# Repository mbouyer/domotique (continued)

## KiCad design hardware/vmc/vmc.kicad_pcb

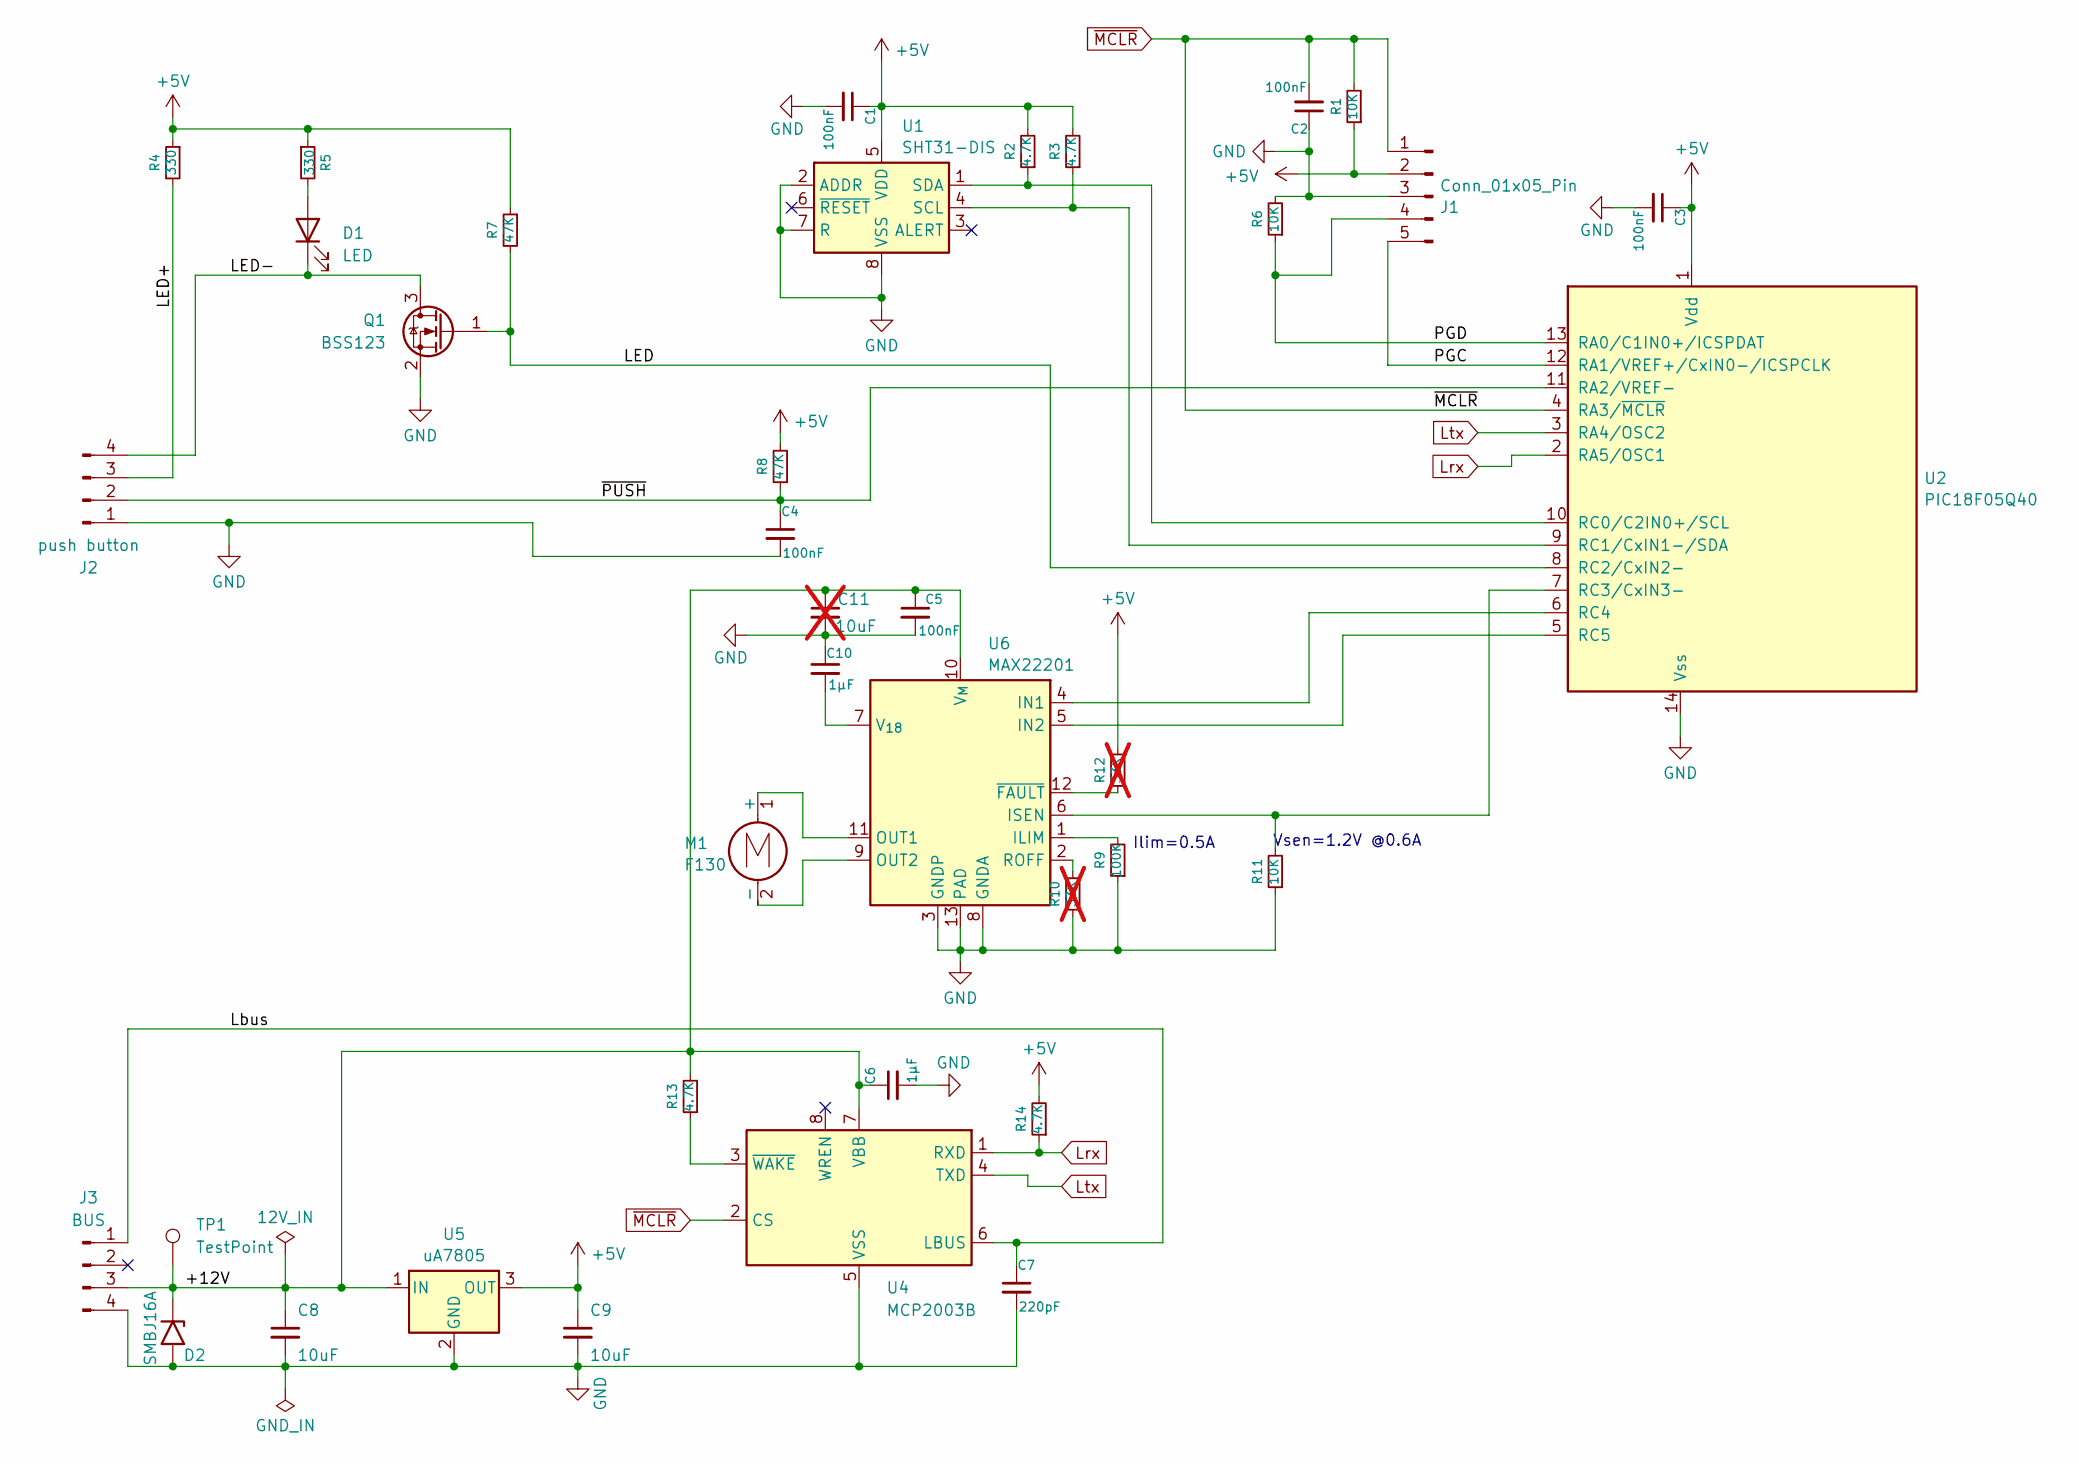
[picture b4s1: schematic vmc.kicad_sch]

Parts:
C1, C2, C3, C4, C5: 100nF; C_0603_1608Metric_Pad1.08x0.95mm_HandSolder
C6: 1µF; C_0805_2012Metric_Pad1.18x1.45mm_HandSolder
C7: 220pF; C_0603_1608Metric_Pad1.08x0.95mm_HandSolder
C8: 10uF; C_1210_3225Metric_Pad1.33x2.70mm_HandSolder
C9: 10uF; C_0805_2012Metric_Pad1.18x1.45mm_HandSolder
C10: 1µF; C_0603_1608Metric_Pad1.08x0.95mm_HandSolder
C11: 10uF; C_1210_3225Metric_Pad1.33x2.70mm_HandSolder; not fitted
D1: LED; LED_0603_1608Metric_Pad1.05x0.95mm_HandSolder
D2: SMBJ16A; D_SMB_Handsoldering
J1: Conn_01x05_Pin; Molex_Pico-SPOX-5-Vertical
J2: push button; Molex Pico-SPOX-4_90
J3: BUS; Molex Pico-SPOX-4_90
M1: F130
Q1: BSS123; SOT-23
R1, R6, R11: 10K; R_0805_2012Metric_Pad1.20x1.40mm_HandSolder
R2, R3, R13, R14: 4.7K; R_0805_2012Metric_Pad1.20x1.40mm_HandSolder
R4, R5: 330; R_0805_2012Metric_Pad1.20x1.40mm_HandSolder
R7, R8: 47K; R_0805_2012Metric_Pad1.20x1.40mm_HandSolder
R9: 100K; R_0805_2012Metric_Pad1.20x1.40mm_HandSolder
R10, R12: 33K; R_0805_2012Metric_Pad1.20x1.40mm_HandSolder; not fitted
TP1: TestPoint; TestPoint_THTPad_D1.5mm_Drill0.7mm
U1: SHT31-DIS; Sensirion_DFN-8-1EP_2.5x2.5mm_P0.5mm_EP1.1x1.7mm
U2: PIC18F05Q40; SOIC-14_3.9x8.7mm_P1.27mm
U4: MCP2003B; SOIC-8_3.9x4.9mm_P1.27mm
U5: uA7805; TO-252-3_TabPin2
U6: MAX22201; Maxim_TDFN-12-1EP_3x3mm_P0.5mm_EP1.7x2.5mm

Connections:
+5V: C1.1, C3.1, C9.1, J1.2, R1.1, R2.2, R3.2, R4.1, R5.1, R7.1, R8.2, R12.2, R14.2, U1.5 (VDD), U2.1 (Vdd), U5.3 (OUT)
/+12V: C5.1, C6.1, C8.1, C11.1, D2.1 (A1), J3.3, R13.2, TP1.1, U4.7 (VBB), U5.1 (IN), U6.10 (V_{M})
/LED: Q1.1 (G), R7.2, U2.8 (RC2/CxIN2-)
/LED+: J2.3, R4.2
/LED-: D1.1 (K), J2.4, Q1.3 (D)
/Lbus: C7.1, J3.1, U4.6 (LBUS)
/PGC: J1.5, U2.12 (RA1/VREF+/CxIN0-/ICSPCLK)
/PGD: J1.4, R6.1, U2.13 (RA0/C1IN0+/ICSPDAT)
/~PUSH: C4.1, J2.2, R8.1, U2.11 (RA2/VREF-)
GND: C1.2, C2.1, C3.2, C4.2, C5.2, C6.2, C7.2, C8.2, C9.2, C10.1, C11.2, D2.2 (A2), J1.3, J2.1, J3.4, Q1.2 (S), R6.2, R9.1, R10.1, R11.1, U1.2 (ADDR), U1.7 (R), U1.8 (VSS), U1.9 (VSS), U2.14 (Vss), U4.5 (VSS), U5.2 (GND), U6.3 (GNDP), U6.8 (GNDA), U6.13 (PAD)
Lrx: R14.1, U2.2 (RA5/OSC1), U4.1 (RXD)
Ltx: U2.3 (RA4/OSC2), U4.4 (TXD)
unnamed: D1.2 (A), R5.2
unnamed: M1.1 (+), U6.11 (OUT1)
unnamed: M1.2 (-), U6.9 (OUT2)
unnamed: R3.1, U1.4 (SCL), U2.9 (RC1/CxIN1-/SDA)
unnamed: R2.1, U1.1 (SDA), U2.10 (RC0/C2IN0+/SCL)
unnamed: R11.2, U2.7 (RC3/CxIN3-), U6.6 (ISEN)
unnamed: U2.6 (RC4), U6.4 (IN1)
unnamed: U2.5 (RC5), U6.5 (IN2)
unnamed: R13.1, U4.3 (~WAKE)
unnamed: R9.2, U6.1 (ILIM)
unnamed: R10.2, U6.2 (ROFF)
unnamed: C10.2, U6.7 (V_{18})
unnamed: R12.1, U6.12 (~FAULT)
~MCLR: C2.2, J1.1, R1.2, U2.4 (RA3/~MCLR), U4.2 (CS)

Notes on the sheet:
Ilim=0.5A
Vsen=1.2V @0.6A

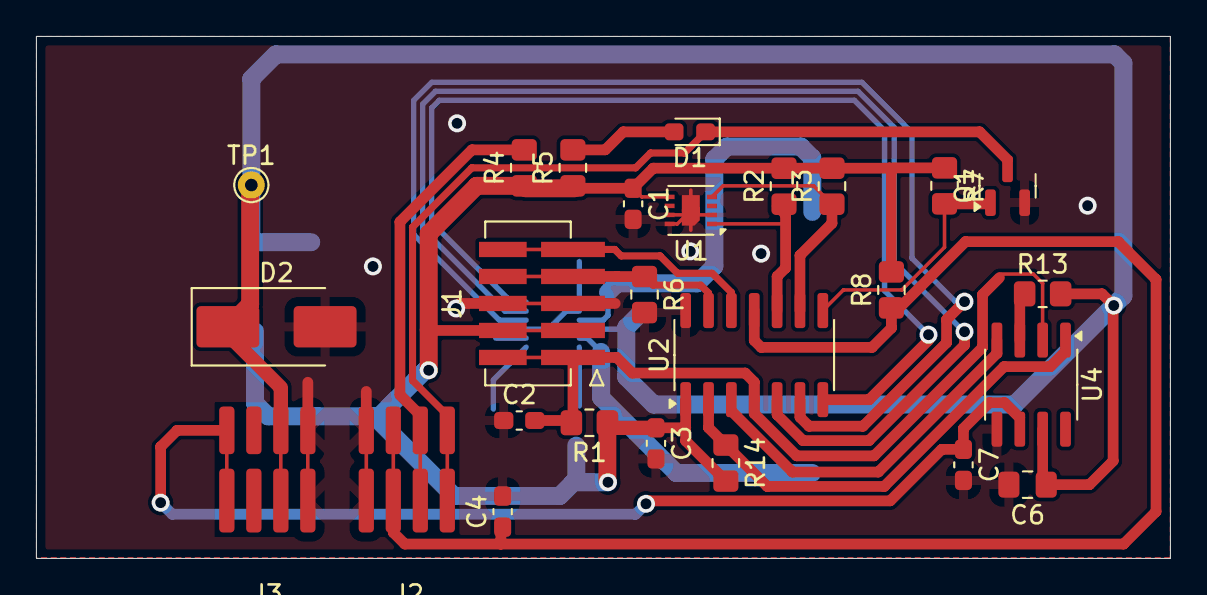
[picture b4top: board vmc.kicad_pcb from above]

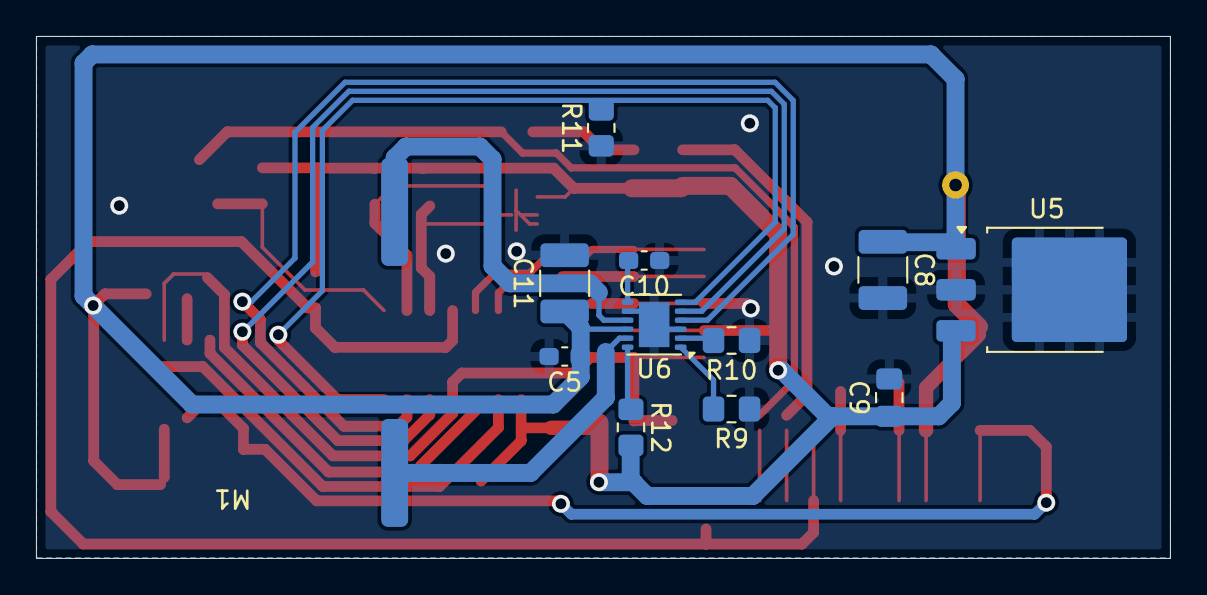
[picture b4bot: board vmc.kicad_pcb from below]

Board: 2 copper layers, 63.0 x 29.0 mm, 38 parts (12 on the bottom side), 26 nets.

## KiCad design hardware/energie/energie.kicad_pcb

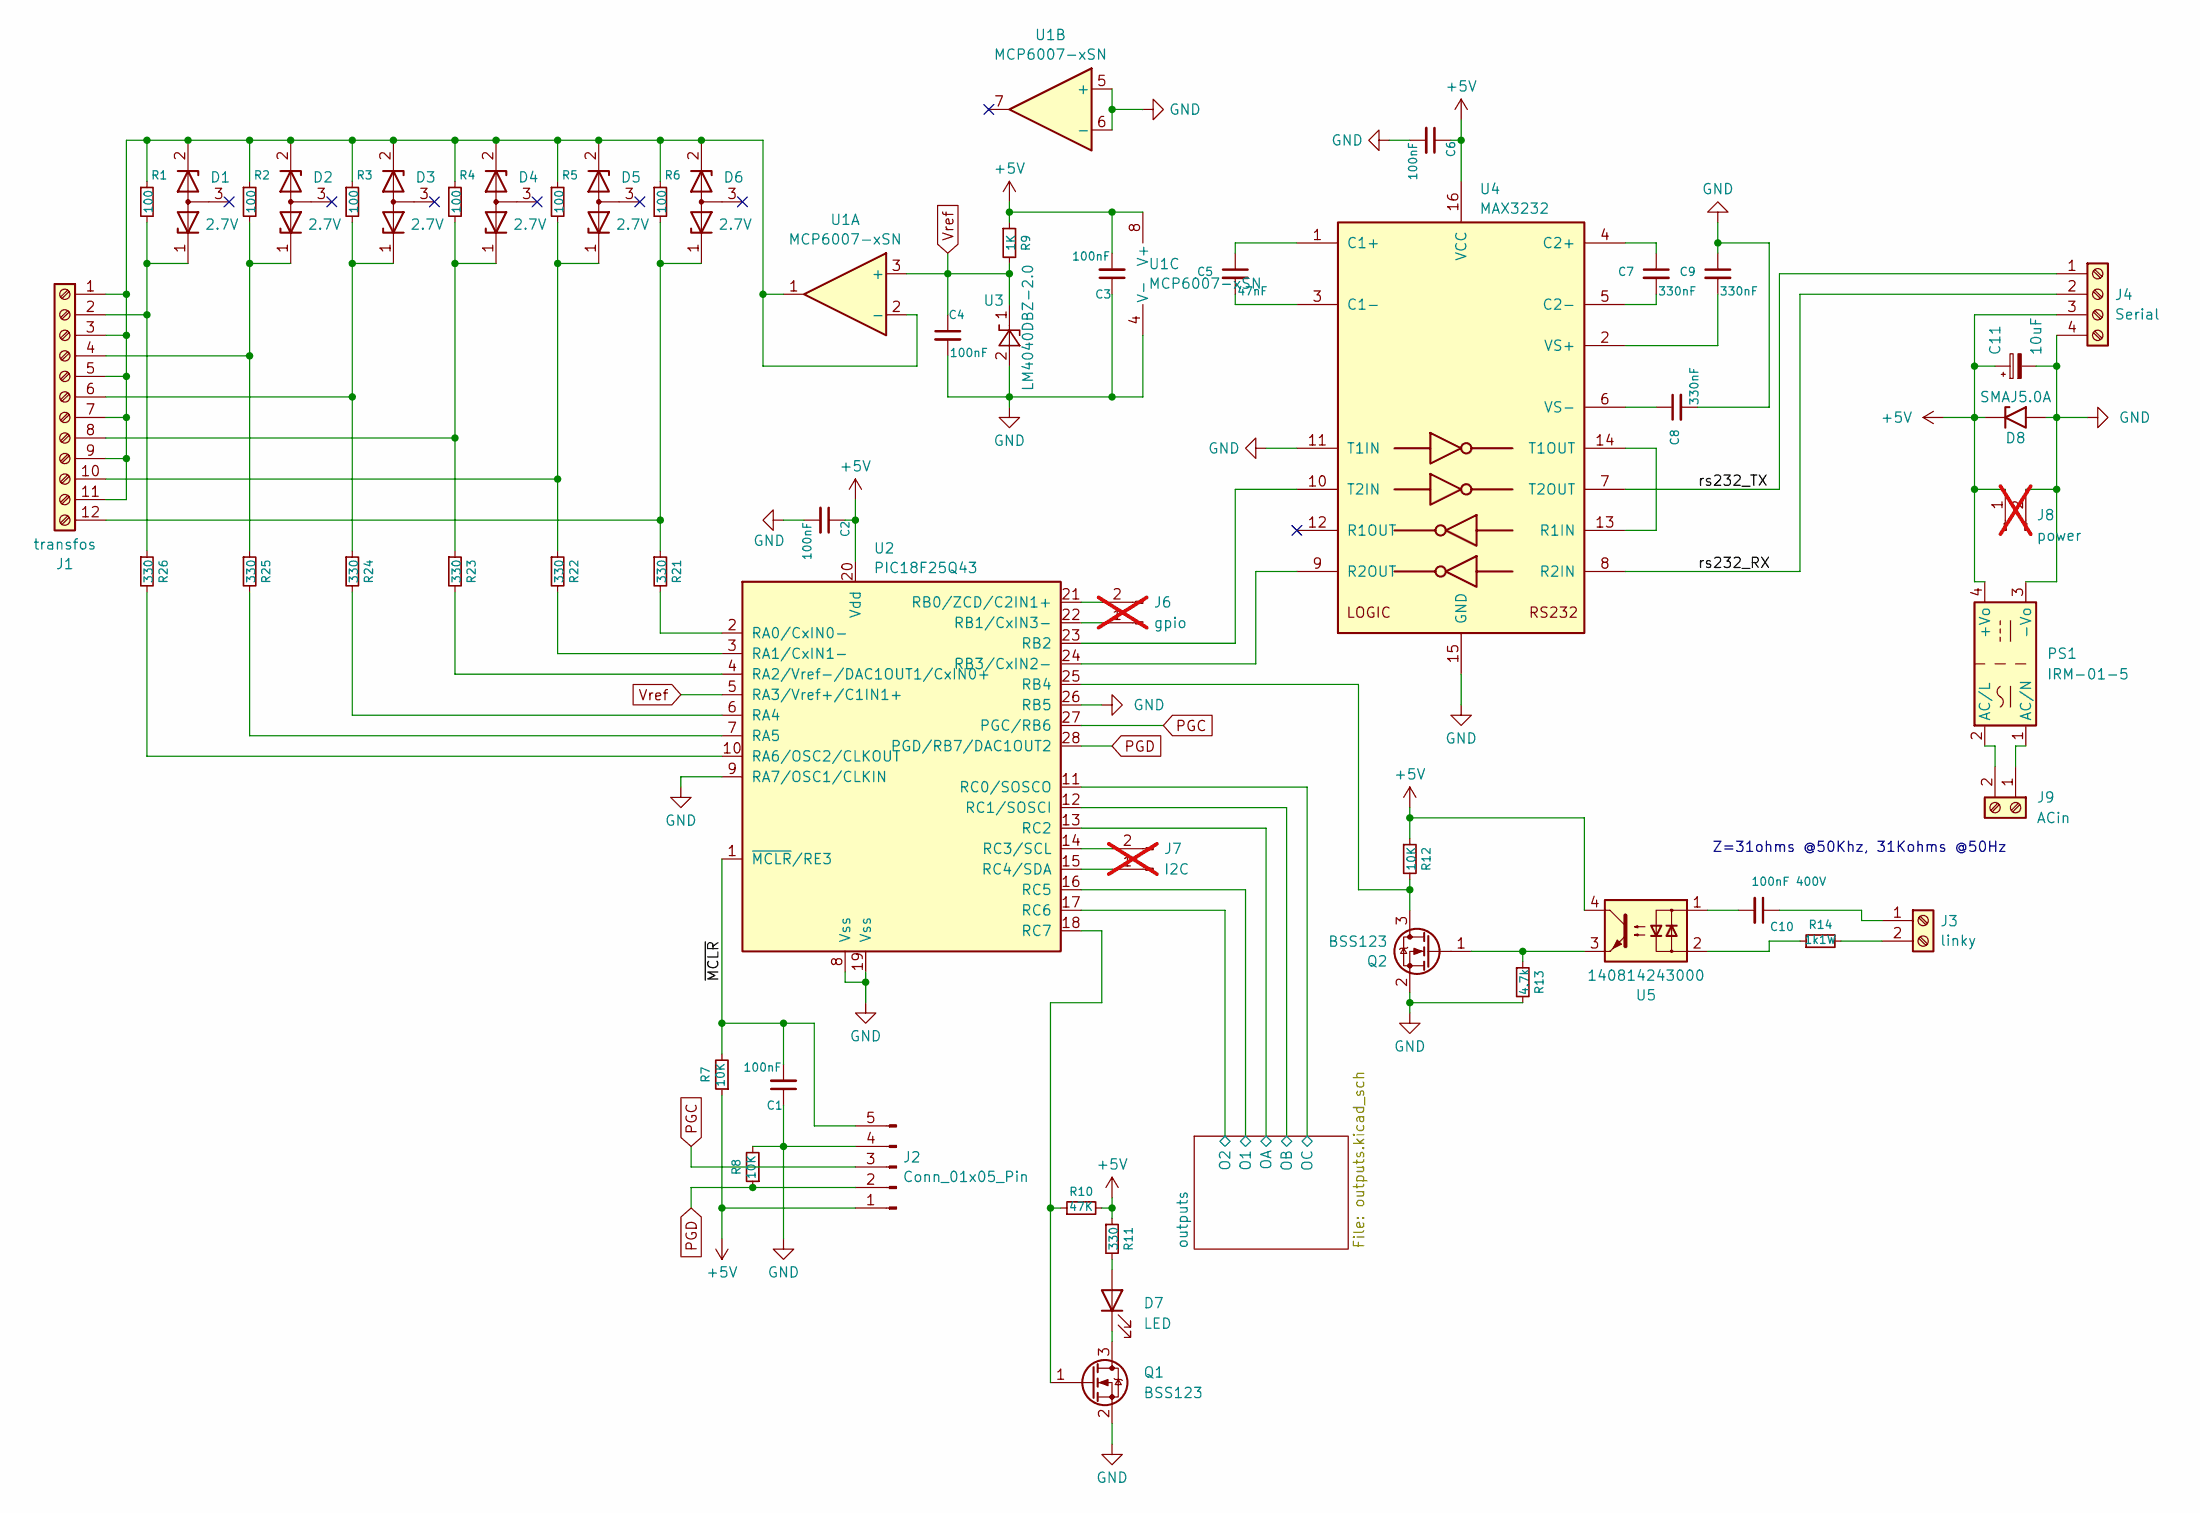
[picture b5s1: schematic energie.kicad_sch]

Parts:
C1, C2, C3, C4, C6: 100nF; C_0603_1608Metric_Pad1.08x0.95mm_HandSolder
C5: 47nF; C_0603_1608Metric_Pad1.08x0.95mm_HandSolder
C7, C8, C9: 330nF; C_0603_1608Metric_Pad1.08x0.95mm_HandSolder
C10: 100nF 400V; C_1808_4520Metric_Pad1.72x2.30mm_HandSolder
C11: 10uF; C_0805_2012Metric_Pad1.18x1.45mm_HandSolder
D1, D2, D3, D4, D5, D6: 2.7V; SOT-23_Handsoldering
D7: LED; LED_0603_1608Metric_Pad1.05x0.95mm_HandSolder
D8: SMAJ5.0A; D_SMA
J1: transfos; PhoenixContact_MCV_1,5_12-G-3.5_1x12_P3.50mm_Vertical
J2: Conn_01x05_Pin; PinHeader_1x05_P2.54mm_Vertical
J3: linky; PhoenixContact_MCV_1,5_2-G-3.5_1x02_P3.50mm_Vertical
J4: Serial; PhoenixContact_MCV_1,5_4-G-3.5_1x04_P3.50mm_Vertical
J6: gpio; PinHeader_1x02_P2.54mm_Vertical_SMD_Pin1Left; not fitted
J7: I2C; PinHeader_1x02_P2.54mm_Vertical_SMD_Pin1Left; not fitted
J8: power; PinHeader_1x02_P2.54mm_Vertical; not fitted
J9: ACin; PhoenixContact_MCV_1,5_2-G-3.5_1x02_P3.50mm_Vertical
PS1: IRM-01-5; Converter_ACDC_MeanWell_IRM-02-xx_THT
Q1, Q2: BSS123; SOT-23
R1, R2, R3, R4, R5, R6: 100; R_0805_2012Metric_Pad1.20x1.40mm_HandSolder
R7, R8, R12: 10K; R_0805_2012Metric_Pad1.20x1.40mm_HandSolder
R9: 1K; R_0805_2012Metric_Pad1.20x1.40mm_HandSolder
R10: 47K; R_0805_2012Metric_Pad1.20x1.40mm_HandSolder
R11, R21, R22, R23, R24, R25, R26: 330; R_0805_2012Metric_Pad1.20x1.40mm_HandSolder
R13: 4.7k; R_0805_2012Metric_Pad1.20x1.40mm_HandSolder
R14: 1k1W; R_2512_6332Metric_Pad1.40x3.35mm_HandSolder
U1: MCP6007-xSN; SOIC-8_3.9x4.9mm_P1.27mm
U2: PIC18F25Q43; SOIC-28W_7.5x18.7mm_P1.27mm
U3: LM4040DBZ-2.0; SOT-23
U4: MAX3232; SOIC-16_3.9x9.9mm_P1.27mm
U5: 140814243000; SMDIP-4_W9.53mm

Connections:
+5V: C2.1, C3.2, C6.1, C11.1, D8.1 (A1), J2.1, J4.3, J8.1, PS1.4 (+Vo), R7.1, R9.1, R10.2, R11.1, R12.1, U1.8 (V+), U2.20 (Vdd), U4.16 (VCC), U5.4
/outputs/O1: U2.16 (RC5); also elsewhere on the board
/outputs/O2: U2.17 (RC6); also elsewhere on the board
/outputs/OA: U2.13 (RC2); also elsewhere on the board
/outputs/OB: U2.12 (RC1/SOSCI); also elsewhere on the board
/outputs/OC: U2.11 (RC0/SOSCO); also elsewhere on the board
/rs232_RX: J4.2, U4.8 (R2IN)
/rs232_TX: J4.1, U4.7 (T2OUT)
/~MCLR: C1.2, J2.5, R7.2, U2.1 (~MCLR/RE3)
GND: C1.1, C2.2, C3.1, C4.2, C6.2, C8.2, C9.1, C11.2, D8.2 (A2), J2.4, J4.4, J8.2, PS1.3 (-Vo), Q1.2 (S), Q2.2 (S), R8.2, R13.2, U1.4 (V-), U1.5 (+), U1.6 (-), U2.8 (Vss), U2.9 (RA7/OSC1/CLKIN), U2.19 (Vss), U2.26 (RB5), U3.2 (A), U4.11 (T1IN), U4.15 (GND)
unnamed: C10.2, U5.1
unnamed: D7.2 (A), R11.2
unnamed: D7.1 (K), Q1.3 (D)
unnamed: D1.2 (K), D2.2 (K), D3.2 (K), D4.2 (K), D5.2 (K), D6.2 (K), J1.1, J1.3, J1.5, J1.7, J1.9, J1.11, R1.1, R2.1, R3.1, R4.1, R5.1, R6.1, U1.1, U1.2 (-)
unnamed: D1.1 (K), J1.2, R1.2, R26.1
unnamed: D2.1 (K), J1.4, R2.2, R25.1
unnamed: D3.1 (K), J1.6, R3.2, R24.1
unnamed: D4.1 (K), J1.8, R4.2, R23.1
unnamed: D5.1 (K), J1.10, R5.2, R22.1
unnamed: D6.1 (K), J1.12, R6.2, R21.1
unnamed: C10.1, J3.1
unnamed: J3.2, R14.2
unnamed: J6.1, U2.22 (RB1/CxIN3-)
unnamed: J6.2, U2.21 (RB0/ZCD/C2IN1+)
unnamed: J7.1, U2.15 (RC4/SDA)
unnamed: J7.2, U2.14 (RC3/SCL)
unnamed: J9.1, PS1.1 (AC/N)
unnamed: J9.2, PS1.2 (AC/L)
unnamed: Q1.1 (G), R10.1, U2.18 (RC7)
unnamed: Q2.3 (D), R12.2, U2.25 (RB4)
unnamed: Q2.1 (G), R13.1, U5.3
unnamed: R14.1, U5.2
unnamed: R21.2, U2.2 (RA0/CxIN0-)
unnamed: R22.2, U2.3 (RA1/CxIN1-)
unnamed: R23.2, U2.4 (RA2/Vref-/DAC1OUT1/CxIN0+)
unnamed: R24.2, U2.6 (RA4)
unnamed: R25.2, U2.7 (RA5)
unnamed: R26.2, U2.10 (RA6/OSC2/CLKOUT)
unnamed: U2.23 (RB2), U4.10 (T2IN)
unnamed: U2.24 (RB3/CxIN2-), U4.9 (R2OUT)
unnamed: C5.1, U4.1 (C1+)
unnamed: C5.2, U4.3 (C1-)
unnamed: C7.1, U4.4 (C2+)
unnamed: C7.2, U4.5 (C2-)
unnamed: U4.13 (R1IN), U4.14 (T1OUT)
unnamed: C9.2, U4.2 (VS+)
unnamed: C8.1, U4.6 (VS-)
PGC: J2.3, U2.27 (PGC/RB6)
PGD: J2.2, R8.1, U2.28 (PGD/RB7/DAC1OUT2)
Vref: C4.1, R9.2, U1.3 (+), U2.5 (RA3/Vref+/C1IN1+), U3.1 (K)

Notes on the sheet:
Z=31ohms @50Khz, 31Kohms @50Hz

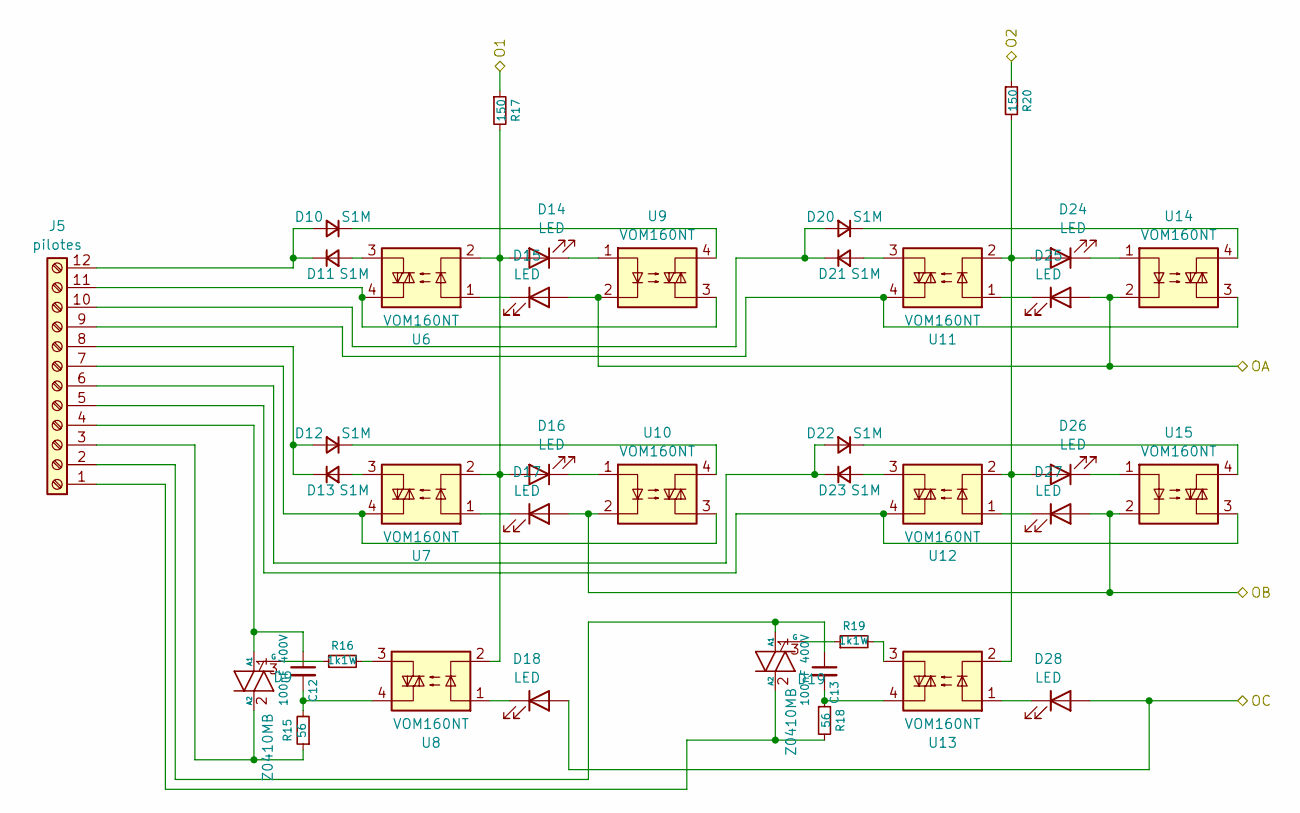
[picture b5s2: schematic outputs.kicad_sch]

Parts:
C12, C13: 100nF 400V; C_1808_4520Metric_Pad1.72x2.30mm_HandSolder
D9, D19: Z0410MB; TO-252-2
D10, D11, D12, D13, D20, D21, D22, D23: S1M; D_SMA
D14, D15, D16, D17, D18, D24, D25, D26, D27, D28: LED; LED_0603_1608Metric_Pad1.05x0.95mm_HandSolder
J5: pilotes; PhoenixContact_MCV_1,5_12-G-3.5_1x12_P3.50mm_Vertical
R15, R18: 56; R_2512_6332Metric_Pad1.40x3.35mm_HandSolder
R16, R19: 1k1W; R_2512_6332Metric_Pad1.40x3.35mm_HandSolder
R17, R20: 150; R_0805_2012Metric_Pad1.20x1.40mm_HandSolder
U6, U7, U8, U9, U10, U11, U12, U13, U14, U15: VOM160NT; VOM160

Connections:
/outputs/O1: R17.1; also elsewhere on the board
/outputs/O2: R20.1; also elsewhere on the board
/outputs/OA: D15.2 (A), D25.2 (A), U9.2, U14.2; also elsewhere on the board
/outputs/OB: D17.2 (A), D27.2 (A), U10.2, U15.2; also elsewhere on the board
/outputs/OC: D18.2 (A), D28.2 (A); also elsewhere on the board
unnamed: C12.2, R15.2, U8.4
unnamed: C13.2, R18.1, U13.4
unnamed: C12.1, D9.1 (A1), J5.4
unnamed: D9.2 (A2), J5.3, R15.1
unnamed: D9.3 (G), R16.1
unnamed: D10.2 (A), D11.1 (K), J5.12
unnamed: D10.1 (K), U9.4
unnamed: D11.2 (A), U6.3
unnamed: D12.2 (A), D13.1 (K), J5.8
unnamed: D12.1 (K), U10.4
unnamed: D13.2 (A), U7.3
unnamed: D14.2 (A), D16.2 (A), R17.2, U6.2, U7.2, U8.2
unnamed: D14.1 (K), U9.1
unnamed: D15.1 (K), U6.1
unnamed: D16.1 (K), U10.1
unnamed: D17.1 (K), U7.1
unnamed: D18.1 (K), U8.1
unnamed: C13.1, D19.1 (A1), J5.2
unnamed: D19.2 (A2), J5.1, R18.2
unnamed: D19.3 (G), R19.1
unnamed: D20.2 (A), D21.1 (K), J5.10
unnamed: D20.1 (K), U14.4
unnamed: D21.2 (A), U11.3
unnamed: D22.2 (A), D23.1 (K), J5.6
unnamed: D22.1 (K), U15.4
unnamed: D23.2 (A), U12.3
unnamed: D24.2 (A), D26.2 (A), R20.2, U11.2, U12.2, U13.2
unnamed: D24.1 (K), U14.1
unnamed: D25.1 (K), U11.1
unnamed: D26.1 (K), U15.1
unnamed: D27.1 (K), U12.1
unnamed: D28.1 (K), U13.1
unnamed: J5.5, U12.4, U15.3
unnamed: J5.7, U7.4, U10.3
unnamed: J5.9, U11.4, U14.3
unnamed: J5.11, U6.4, U9.3
unnamed: R16.2, U8.3
unnamed: R19.2, U13.3

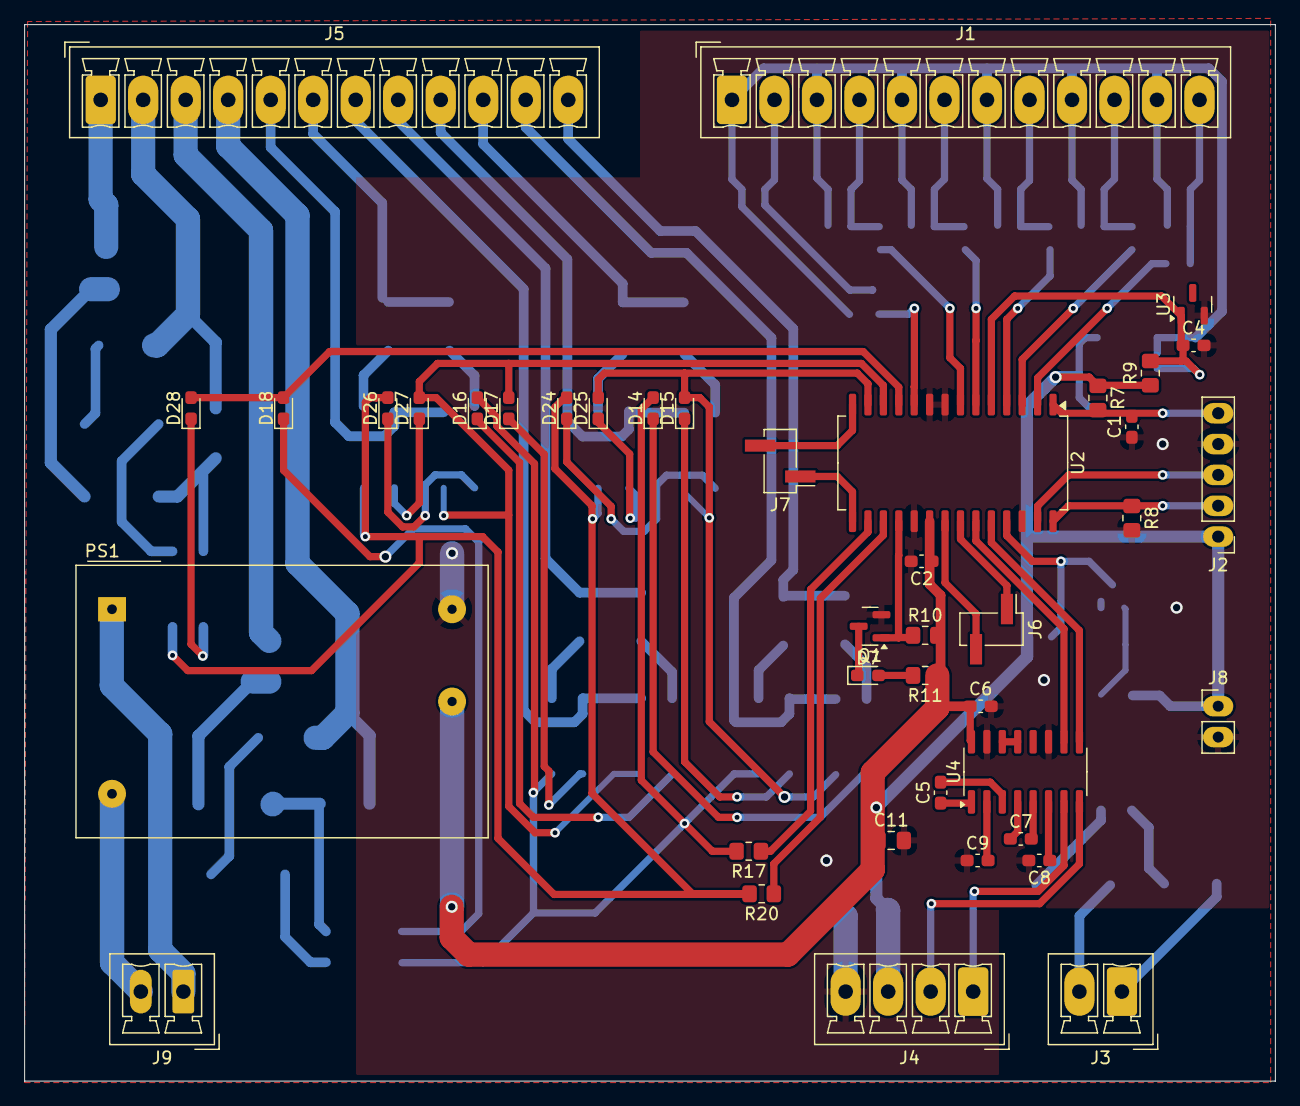
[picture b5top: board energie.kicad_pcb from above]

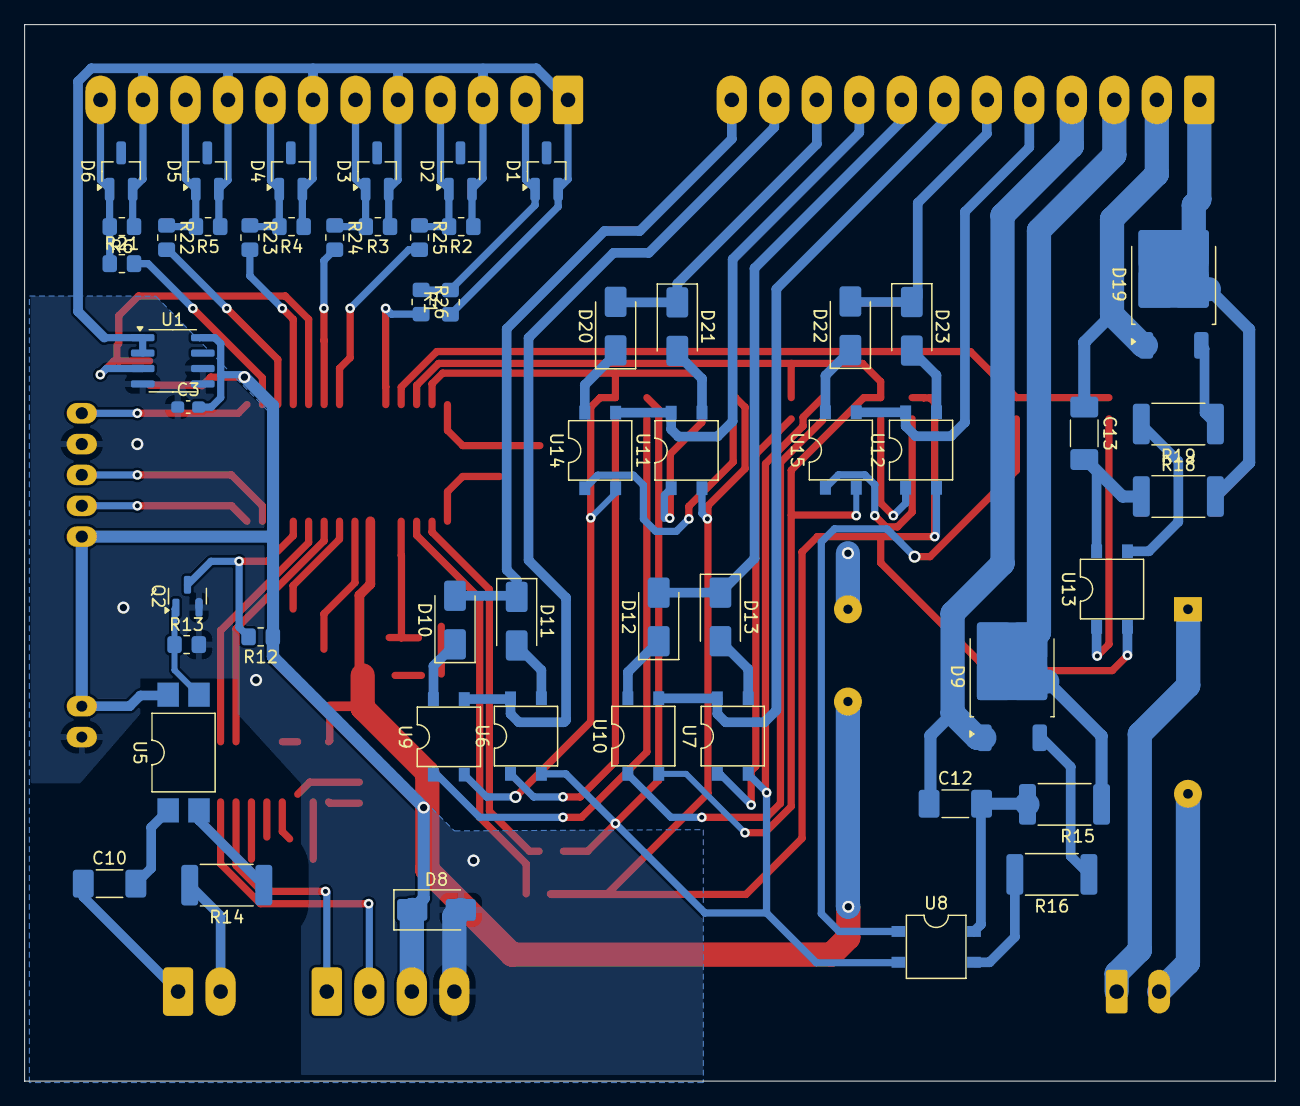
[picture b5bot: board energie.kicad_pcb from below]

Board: 2 copper layers, 103.0 x 87.0 mm, 94 parts (53 on the bottom side), 88 nets.

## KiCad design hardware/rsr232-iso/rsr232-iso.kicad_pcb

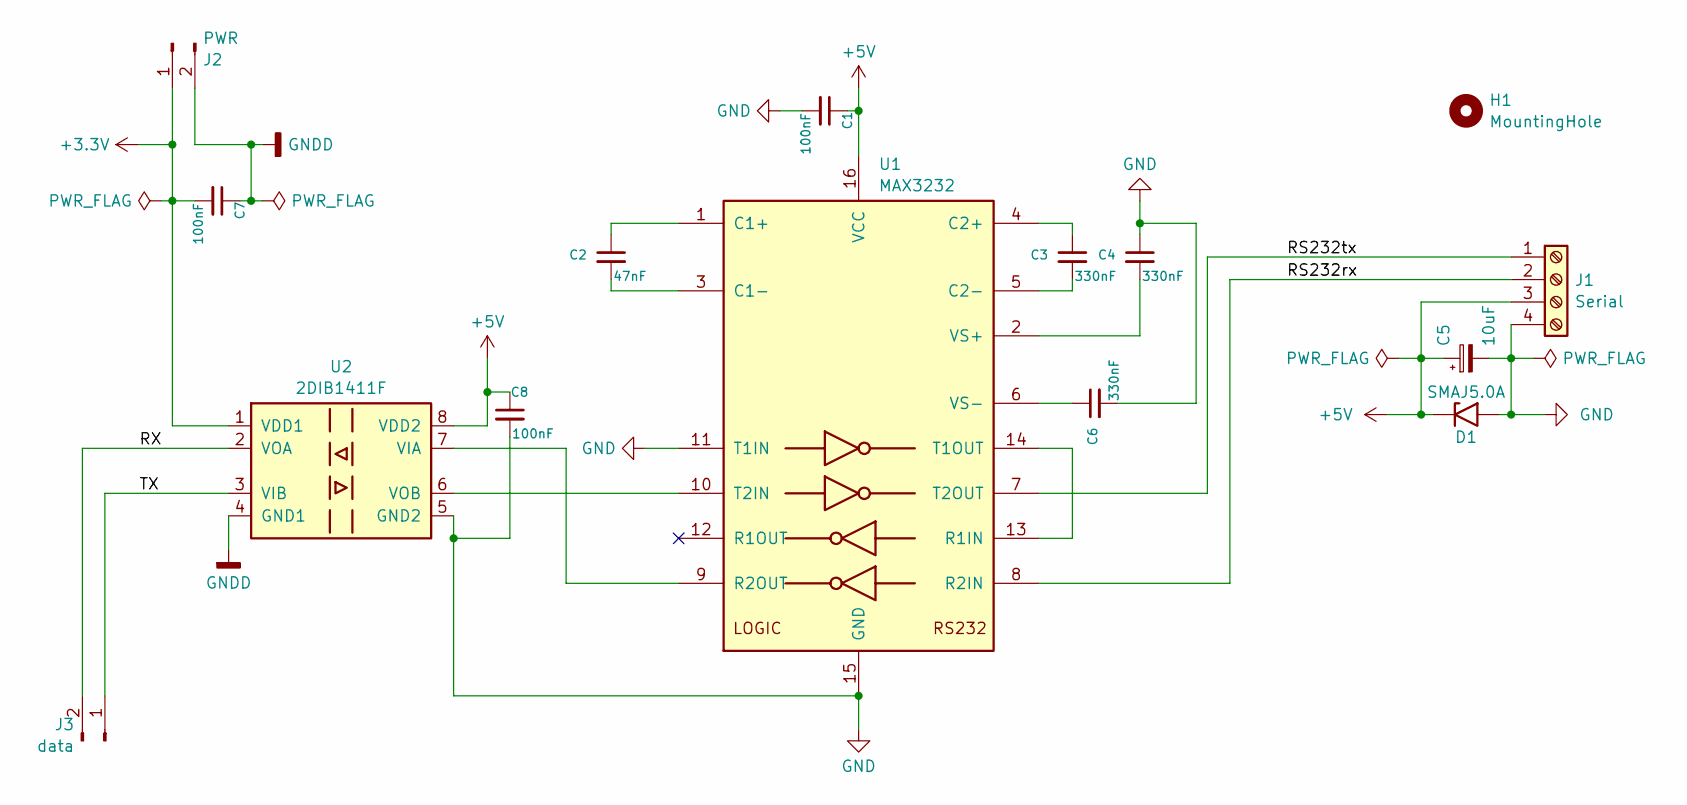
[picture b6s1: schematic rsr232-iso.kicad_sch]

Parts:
C1, C7, C8: 100nF; C_0603_1608Metric_Pad1.08x0.95mm_HandSolder
C2: 47nF; C_0603_1608Metric_Pad1.08x0.95mm_HandSolder
C3, C4, C6: 330nF; C_0603_1608Metric_Pad1.08x0.95mm_HandSolder
C5: 10uF; C_0805_2012Metric_Pad1.18x1.45mm_HandSolder
D1: SMAJ5.0A; D_SMA
H1: MountingHole; MountingHole_3.2mm_M3_DIN965
J1: Serial; PhoenixContact_MCV_1,5_4-G-3.5_1x04_P3.50mm_Vertical
J2: PWR; PinHeader_1x02_P2.54mm_Vertical
J3: data; PinHeader_1x02_P2.54mm_Vertical
U1: MAX3232; SOIC-16_3.9x9.9mm_P1.27mm
U2: 2DIB1411F; SOIC-8_3.9x4.9mm_P1.27mm

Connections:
+3.3V: C7.2, J2.1, U2.1 (VDD1)
+5V: C1.1, C5.1, C8.1, D1.1 (A1), J1.3, U1.16 (VCC), U2.8 (VDD2)
/RS232rx: J1.2, U1.8 (R2IN)
/RS232tx: J1.1, U1.7 (T2OUT)
/RX: J3.2, U2.2 (VOA)
/TX: J3.1, U2.3 (VIB)
GND: C1.2, C4.1, C5.2, C6.2, C8.2, D1.2 (A2), J1.4, U1.11 (T1IN), U1.15 (GND), U2.5 (GND2)
GNDD: C7.1, J2.2, U2.4 (GND1)
unnamed: C2.1, U1.1 (C1+)
unnamed: C2.2, U1.3 (C1-)
unnamed: C3.1, U1.4 (C2+)
unnamed: C3.2, U1.5 (C2-)
unnamed: U1.13 (R1IN), U1.14 (T1OUT)
unnamed: U1.9 (R2OUT), U2.7 (VIA)
unnamed: U1.10 (T2IN), U2.6 (VOB)
unnamed: C4.2, U1.2 (VS+)
unnamed: C6.1, U1.6 (VS-)

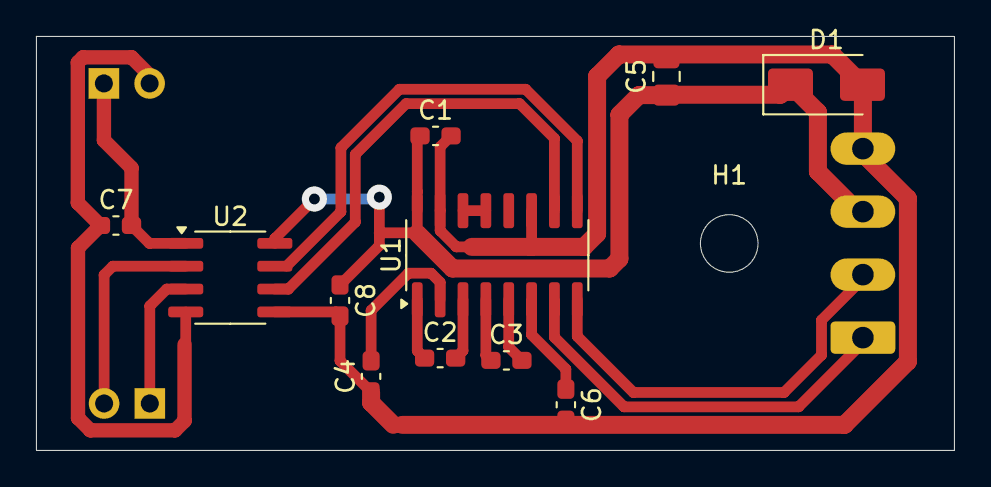
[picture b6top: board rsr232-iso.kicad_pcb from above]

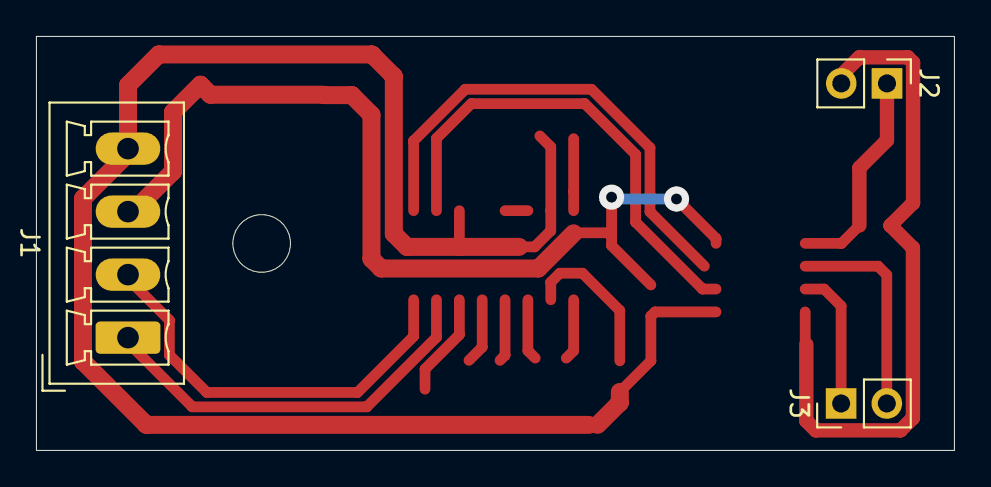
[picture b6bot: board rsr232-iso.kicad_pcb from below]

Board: 2 copper layers, 51.0 x 23.0 mm, 15 parts (3 on the bottom side), 17 nets.

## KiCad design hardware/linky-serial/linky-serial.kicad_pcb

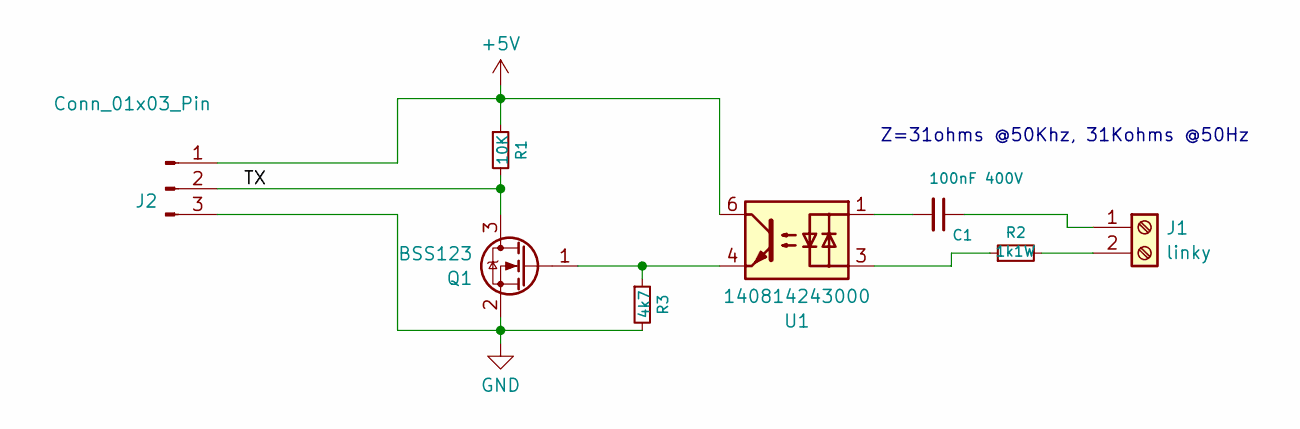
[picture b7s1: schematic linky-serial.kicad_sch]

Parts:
C1: 100nF 400V; C_1812_4532Metric
J1: linky; PhoenixContact_MCV_1,5_2-G-3.5_1x02_P3.50mm_Vertical
J2: Conn_01x03_Pin; PinHeader_1x03_P2.54mm_Vertical
Q1: BSS123; SOT-23
R1: 10K; R_0805_2012Metric_Pad1.20x1.40mm_HandSolder
R2: 1k1W; R_2512_6332Metric_Pad1.40x3.35mm_HandSolder
R3: 4k7; R_0805_2012Metric_Pad1.20x1.40mm_HandSolder
U1: 140814243000; MFSOP6-4_4.4x3.6mm_P1.27mm

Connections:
+5V: J2.1, R1.1, U1.6
/TX: J2.2, Q1.3 (D), R1.2
GND: J2.3, Q1.2 (S), R3.2
unnamed: C1.2, U1.1
unnamed: C1.1, J1.1
unnamed: J1.2, R2.2
unnamed: Q1.1 (G), R3.1, U1.4
unnamed: R2.1, U1.3

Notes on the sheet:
Z=31ohms @50Khz, 31Kohms @50Hz

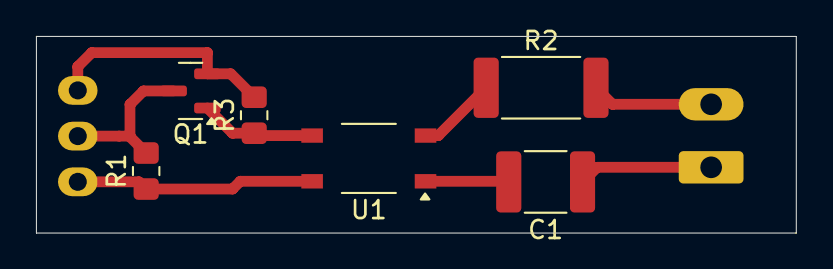
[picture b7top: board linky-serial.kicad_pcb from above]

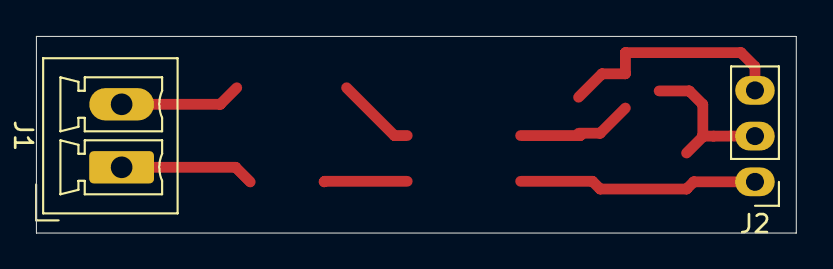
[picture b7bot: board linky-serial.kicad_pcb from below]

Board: 2 copper layers, 42.2 x 10.9 mm, 8 parts (2 on the bottom side), 8 nets.

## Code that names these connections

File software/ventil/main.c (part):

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 * port outputs and definitions
 */

#define	O_LED	(u_char)0x04 /* RA2 */
#define LED	LATAbits.LATA2
#define O_I2C	(u_char)0x03 /* RC0, RC1 */

#define M_N	0x20	/* RC5 */
#define M_S	0x08	/* RC3 */
#define M_E	0x04	/* RC2 */
#define M_O	0x10	/* RC4 */

static uint8_t motor_o[] = {
	M_N,
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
